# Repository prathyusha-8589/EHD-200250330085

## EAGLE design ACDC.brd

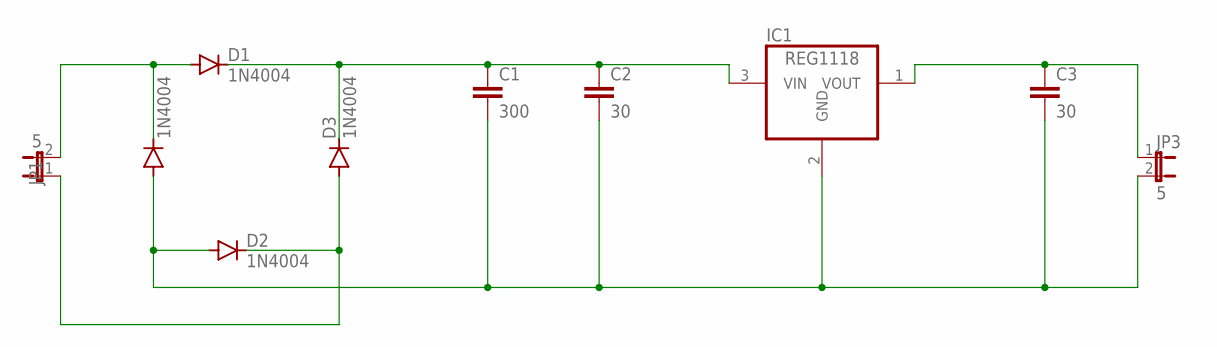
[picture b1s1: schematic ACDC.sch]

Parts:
C1: 300; C2.5-3
C2, C3: 30; C2.5-3
D1, D2, D3, D4: 1N4004; DO41-10
IC1: REG1118; SOT223
JP1, JP3: 5; JP1

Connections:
unnamed: D1.A, D4.C, JP1.2
unnamed: C1.1, C2.1, D1.C, D3.C, IC1.3 (VIN)
unnamed: D2.C, D3.A, JP1.1
unnamed: C1.2, C2.2, C3.2, D2.A, D4.A, IC1.2 (GND), JP3.2
unnamed: C3.1, IC1.1 (VOUT), JP3.1

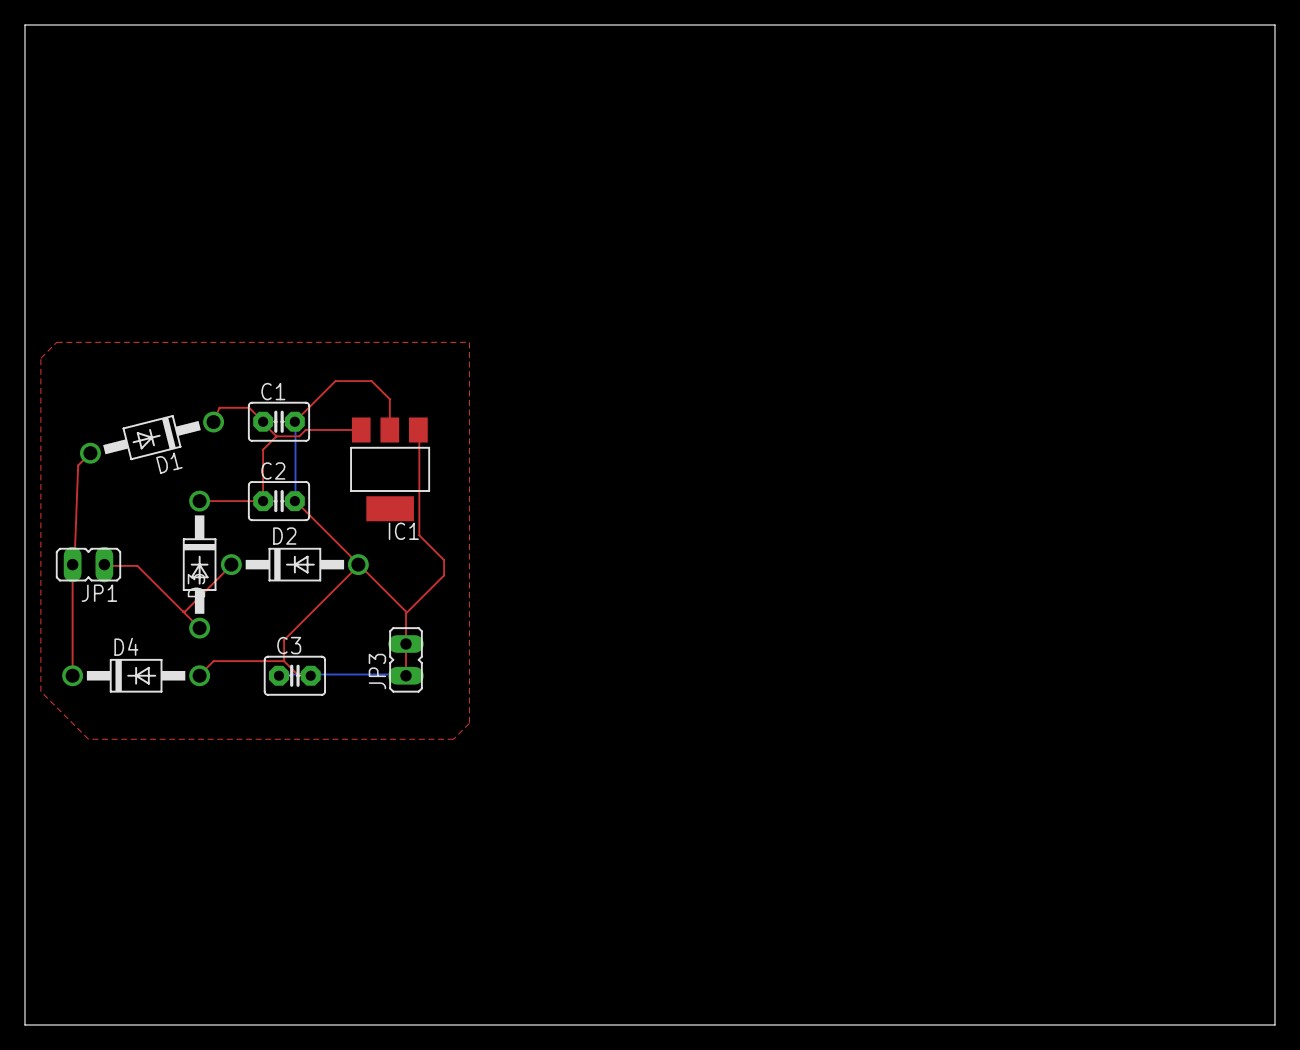
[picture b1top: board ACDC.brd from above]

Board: 2 copper layers, 100.0 x 80.0 mm, 10 parts (0 on the bottom side), 5 nets.

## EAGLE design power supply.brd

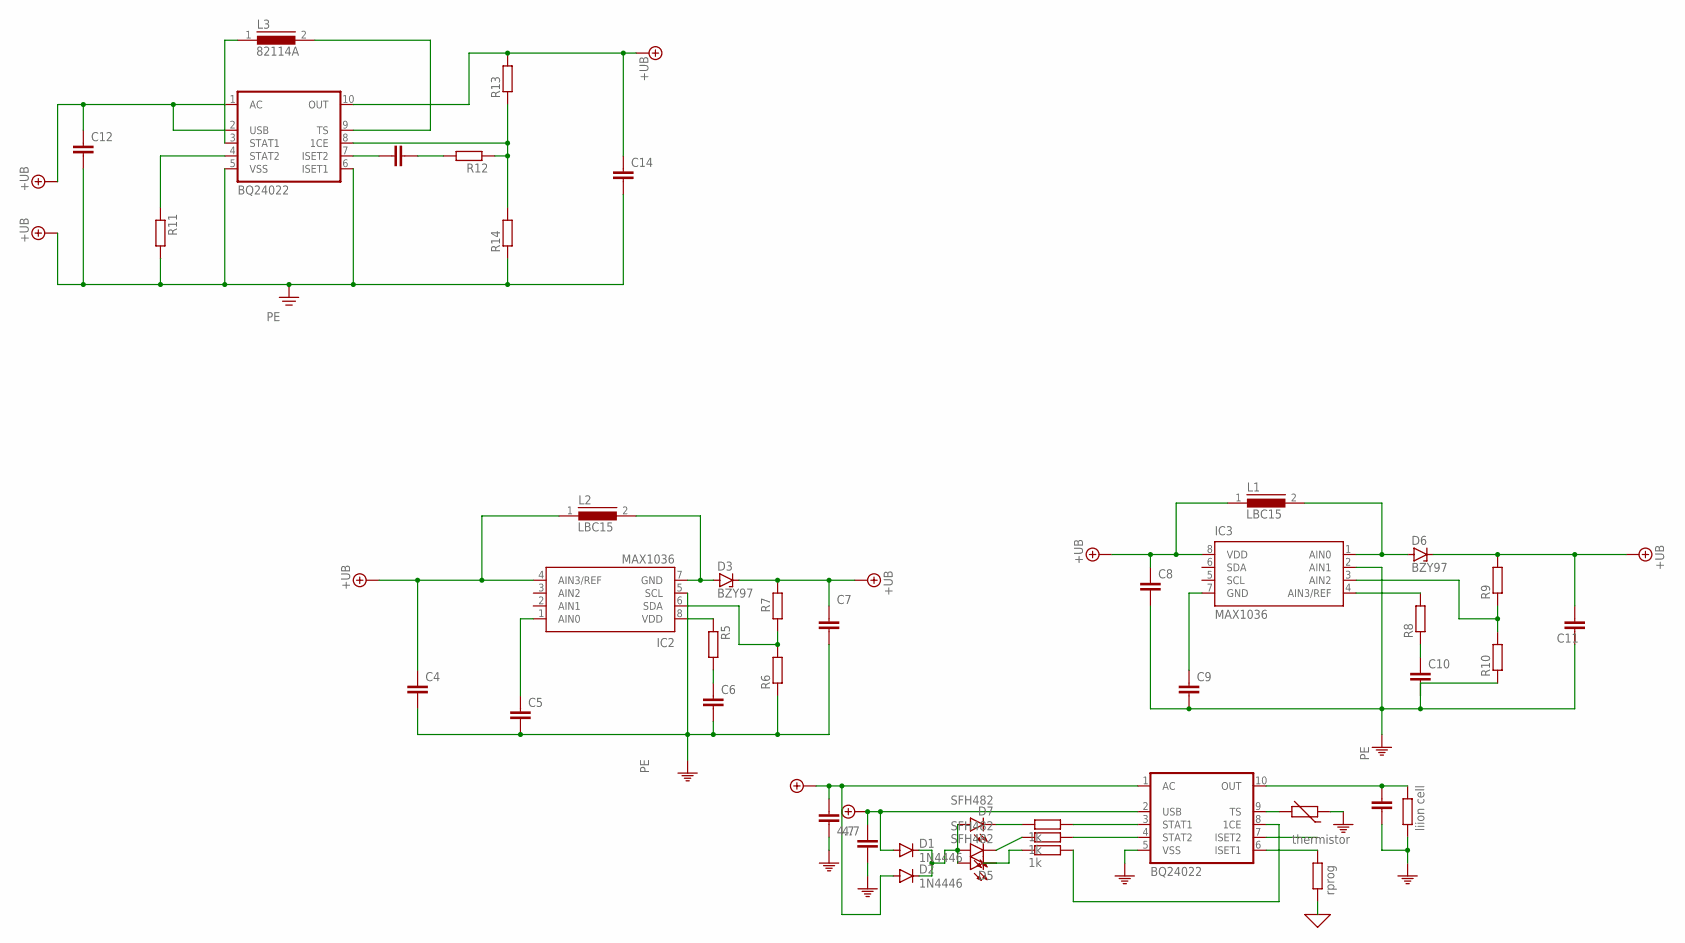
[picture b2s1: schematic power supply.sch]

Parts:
C1, C2: 4.7; C2.5-3
C3, C4, C5, C6, C7, C8, C9, C10, C11, C12, C13, C14: C2,5-3; C2.5-3
D1, D2: 1N4446; DO35-10
D3, D6: BZY97; F126Z12
D4, D5, D7: SFH482
IC1, IC4: BQ24022; DRC-S-PVSON-N10
IC2, IC3: MAX1036; SOT23-8L
L1, L2: LBC15
L3: 82114A
LIIONCELL: liion cell; 0204V
R1, R2, R3: 1k; 0204V
R4: rprog; 0204V
R5, R6, R7, R8, R9, R10, R11, R12, R13, R14: R-EU_0204/2V; 0204V
THERMISTOR: thermistor; R-5

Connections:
0: R4.1
+UB: C1.1, C2.2, C4.1, C7.1, C8.1, C11.1, C12.1, C12.2, C14.1, C14.2, D1.A, D2.A, D3.C, D6.C, IC1.1 (AC), IC1.2 (USB), IC2.4 (AIN3/REF), IC3.8 (VDD), IC4.1 (AC), IC4.2 (USB), IC4.5 (VSS), IC4.6 (ISET1), IC4.10 (OUT), L1.1, L2.1, R7.2, R9.2, R11.2, R13.2, R14.1
unnamed: D7.K (C), R1.1
unnamed: IC1.3 (STAT1), R1.2
unnamed: IC1.4 (STAT2), R2.2
unnamed: D4.K (C), R2.1
unnamed: C6.1, R5.2
unnamed: D1.C, D2.C
unnamed: IC1.6 (ISET1), R4.2
unnamed: IC1.8 (1CE), R3.2
unnamed: IC1.9 (TS), THERMISTOR.2
unnamed: D5.K (C), R3.1
unnamed: C3.1, IC1.10 (OUT), LIIONCELL.2
unnamed: D4.A, D5.A, D7.A
unnamed: C9.1, IC3.7 (GND)
unnamed: D3.A, IC2.7 (GND), L2.2
unnamed: C5.1, IC2.1 (AIN0)
unnamed: D6.A, IC3.1 (AIN0), L1.2
unnamed: IC2.8 (VDD), R5.1
unnamed: IC2.6 (SDA), R6.2, R7.1
unnamed: C10.1, R8.1
unnamed: IC3.4 (AIN3/REF), R8.2
unnamed: C13.1, IC4.7 (ISET2)
unnamed: C13.2, R12.2
unnamed: IC3.3 (AIN2), R9.1, R10.2
unnamed: IC4.4 (STAT2), R11.1
unnamed: IC4.3 (STAT1), L3.1
unnamed: IC4.9 (TS), L3.2
unnamed: IC4.8 (1CE), R12.1, R13.1, R14.2
PE: C1.2, C2.1, C3.2, C4.2, C5.2, C6.2, C7.2, C8.2, C9.2, C10.2, C11.2, IC1.5 (VSS), IC2.5 (SCL), IC3.2 (AIN1), LIIONCELL.1, R6.1, R10.1, THERMISTOR.1

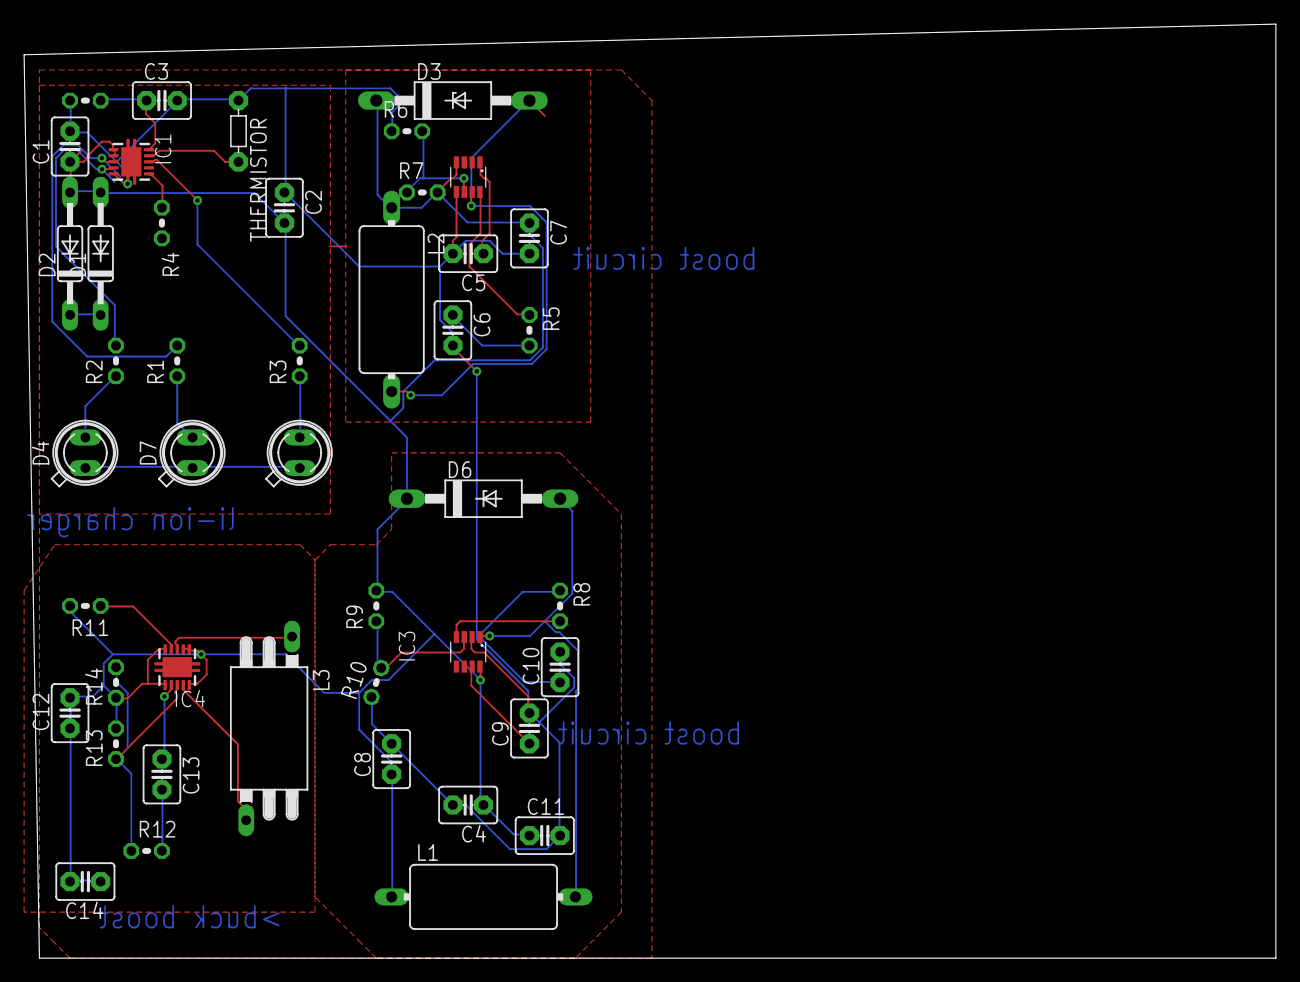
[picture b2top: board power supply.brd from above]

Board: 2 copper layers, 103.8 x 77.5 mm, 44 parts (0 on the bottom side), 29 nets.
